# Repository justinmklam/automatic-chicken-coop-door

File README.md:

# Automatic Chicken Coop Door

Automatic chicken coop door for my backyard egg layers. Modeled after the commercially available [Chicken Guard](https://www.chickenguard.com/).

## Parts List
- Arduino Pro Mini
- Monochrome 128x32 I2C OLED
- DS3231 RTC with CR2032 Battery
- 6V 10rpm 25GA Brushed DC Motor
- TB6612FNG Motor Driver
- XL6009 Buck Boost Module

## Dependencies
- [Low Power](https://github.com/rocketscream/Low-Power)
- [Motor Driver TB6612FNG](https://github.com/sparkfun/SparkFun_TB6612FNG_Arduino_Library)
- [FabioCuomo-DS3231](https://github.com/FabioCuomo/FabioCuomo-DS3231)
- [SSD1306 1.2.9](https://github.com/adafruit/Adafruit_SSD1306)
- [GFX 1.4.2](https://github.com/adafruit/Adafruit-GFX-Library)

## How It Works

The main program sets alarms to wake up from sleep based on sunrise/sunset times (from [here](https://www.timeanddate.com/sun/canada/vancouver?month=1&year=2019)). These times are consistent year after year, and is more reliable than using a light sensor which can be finicky to adjust for street lamps, headlights from passing cars, etc.

## Power Consumption

- Powered on = 18.35 mA
- Motor on = 320 mA (no load), ~700 mA (load)
- Sleep = 0.94 mA

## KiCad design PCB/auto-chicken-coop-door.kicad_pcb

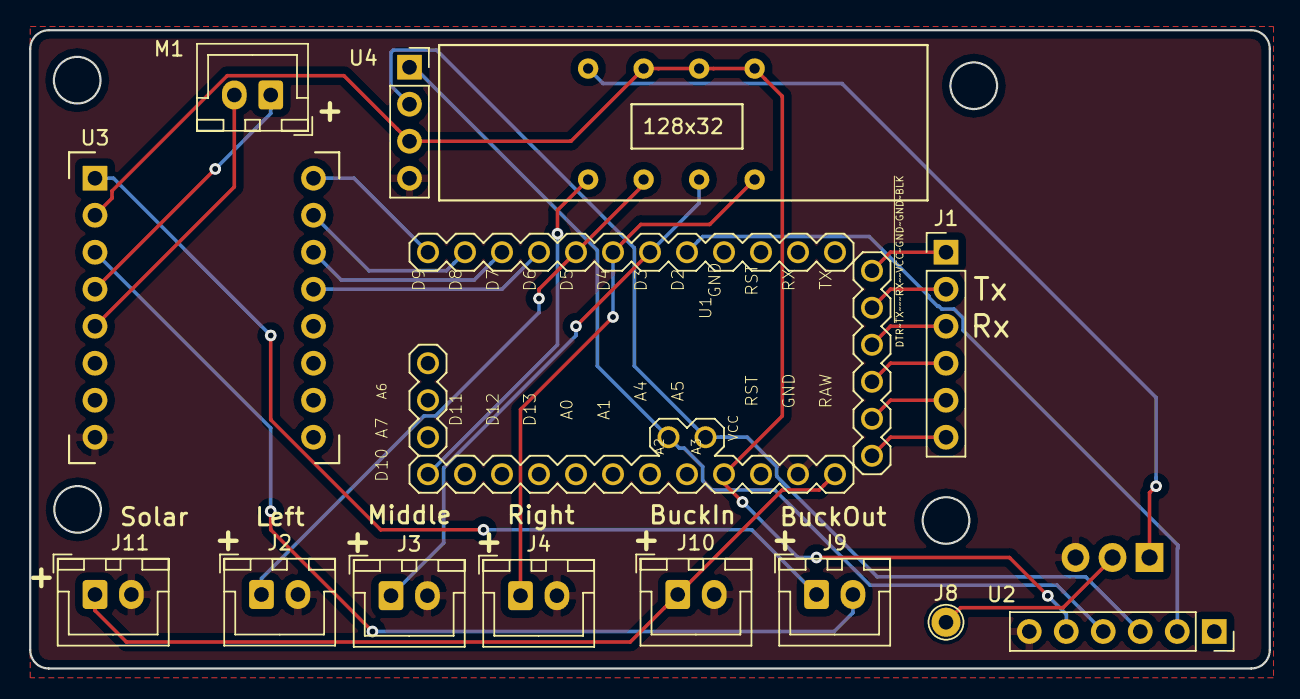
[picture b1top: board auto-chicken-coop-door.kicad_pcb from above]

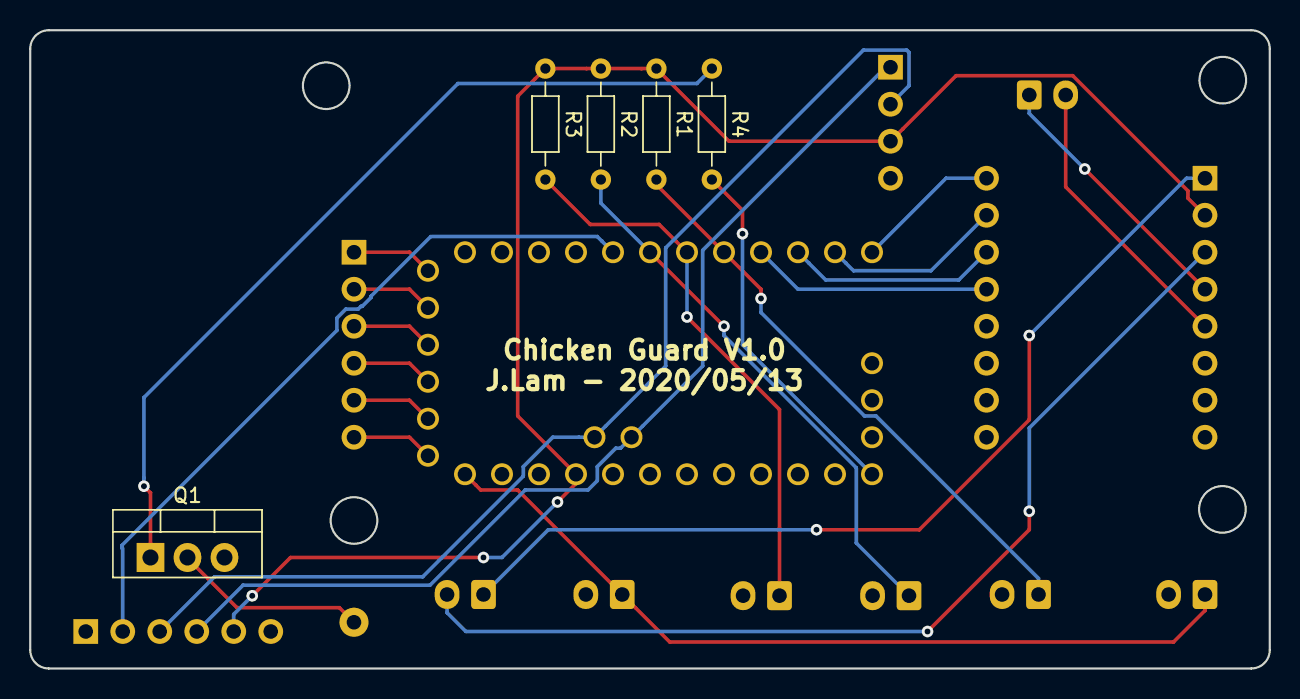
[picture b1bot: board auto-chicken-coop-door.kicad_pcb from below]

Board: 2 copper layers, 85.1 x 43.8 mm, 18 parts (5 on the bottom side), 26 nets.

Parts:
J1: Programming_Headers; PinHeader_1x06_P2.54mm_Vertical
J2: Conn_Left; JST_XH_B02B-XH-A_1x02_P2.50mm_Vertical
J3: Conn_Middle; JST_XH_B02B-XH-A_1x02_P2.50mm_Vertical
J4: Conn_Right; JST_XH_B02B-XH-A_1x02_P2.50mm_Vertical
J8: Conn_01x01; TestPoint_THTPad_D2.0mm_Drill1.0mm
J9: BuckBoost; JST_XH_B02B-XH-A_1x02_P2.50mm_Vertical
J10, J11: Charger; JST_XH_B02B-XH-A_1x02_P2.50mm_Vertical
M1: Motor_DC; JST_XH_B02B-XH-A_1x02_P2.50mm_Vertical
Q1: TIP122; TO-220-3_Vertical
R1, R2, R3: 10k; R_Axial_DIN0204_L3.6mm_D1.6mm_P7.62mm_Horizontal
R4: 1k; R_Axial_DIN0204_L3.6mm_D1.6mm_P7.62mm_Horizontal
U1: Arduino_Pro_Mini; ArduinoProMini
U2: DS3231; PinSocket_1x06_P2.54mm_Vertical
U3: Sparkfun_Dual_Motor_Driver_TB6612FNG; Sparkfun_TB6612FNG
U4: SSD1306_OLED_128x32; SSD1306_Adafruit_128x32

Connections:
D3: J3.1, R2.2, U1.D3
D4: J4.1, R3.2, U1.D4
D5: J2.1, R1.2, U1.D5
D10: R4.2, U1.D10
GND: J2.2, J3.2, J4.2, J10.2, J11.2, Q1.3, U1.GND@1, U2.6, U3.8, U4.4
unnamed: J1.1, U1.DTR
unnamed: J1.2, U1.TX@1
unnamed: J1.3, U1.RX@1
unnamed: J1.4, U1.VCC@1
unnamed: J1.5, U1.GND@2
unnamed: J1.6, U1.BLK
unnamed: J8.1, Q1.2
unnamed: J9.1, U3.1
unnamed: J9.2, U3.3
unnamed: J10.1, J11.1, U1.RAW
unnamed: M1.1, U3.4
unnamed: M1.2, U3.5
unnamed: Q1.1, R4.1
unnamed: U1.D2, U2.2
unnamed: U1.D6, U3.12
unnamed: U1.D7, U3.11
unnamed: U1.D8, U3.10
unnamed: U1.D9, U3.9
SCL: U1.A5, U2.3, U4.2
SDA: U1.A4, U2.4, U4.1
VCC: R1.1, R2.1, R3.1, U1.VCC, U2.5, U3.2, U4.3

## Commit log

2019-03-03 Add test code for controlling motor driver
2019-03-04 Add motor firmware settings from config utility
2019-03-09 Refactor motor control methods and base sketch
2019-03-09 Refactor motor control to class
2019-03-09 Final working demo implemented
2019-03-09 Move defines to header; rename move() to setSpeed()
2019-03-09 Add vscode project settings
2019-03-09 Trim trailing whitespace
2019-03-15 Add 3D print models for motor spool
2019-03-15 Initial commit of main controller sketch
2019-03-20 Add arduino libraries to path
2019-03-20 Use RTClibExtended for alarms; add low power example
2019-03-20 Change date/timestamp methods to directly return the string
2019-03-22 Move clear_alarms() to begin()
2019-03-22 Add wrapper class for ssd1306 display
2019-03-22 Minor fixes to display and rtc functions
2019-03-22 Reordered include paths so manually downloaded libs are found first
2019-03-22 Add wrapper class for motor control
    Should refactor class to use inheritance instead
2019-03-23 Pad date/time formats with leading 0
2019-03-23 Add basic button functionality
2019-03-23 Change defined variables to const
2019-03-23 Add proper display sleep method
    Reduces sleep consumption from ~2mA to ~0.8mA
2019-03-23 Fix millis() interval check to handle rollover
2019-03-23 Minor improvements to rtc and display methods
    Replace malloc with input buffer so don't need to free memory. Was
    causing timestamp to not show on display after a few mins.
    Remove display() from methods to prevent double refresh.
    Moved global variables to loop(), but didn't seem to affect memory.
2019-03-23 Move standby calls to functions; add initial inactive sleep method
2019-03-24 [major] Refactor using task schedulers
2019-03-24 Add build output
2019-03-24 Minor reformatting changes
2019-03-24 Separate sleep mode from inactivity and alarm
    Also add inactivity sleep to user input
2019-03-25 Add preliminary door calibration method
2019-04-09 Add ipch files to gitignore
2019-04-09 Implement basic door open/close and calibration method
2019-04-09 Save calibrated distance to eeprom
2019-04-09 Activate calibration after 2 second button press
2019-04-09 Move door calibration to separate function
2019-04-09 Move custom eeprom methods to separate file
2019-04-09 Rename constants to upper case
2019-04-09 [major] Create door control triggered task
2019-04-09 Add RTC getter for now()
2019-04-09 Initial commit of sunrise/sunset alarm class (untested)
2019-04-09 Fix logic for sunrise/sunset alarms
2019-04-09 [major] Add logger
2019-04-09 Add door control after waking from sleep
2019-04-09 Add note to logger
2019-04-09 Show next alarm on main display
2019-04-09 Write door open/close status to EEPROM
2019-04-10 Fix garbage display output
2019-04-10 Add TODO about artifacts on screen
2019-04-10 Minor edits to logger
2019-04-10 Minor formatting edits
2019-04-10 [bugfix] Correct current time check so next alarm is set correctly
2019-04-10 Autoformat documents
2019-04-10 Rename driver files
2019-04-10 Move jrk21v3 config to sketch folder
2019-04-10 Rename project folder
2019-04-10 Reduce frequency of alarm set
2019-04-10 Move jrk21v3 demo to separate repository
2019-04-10 Added image of chickens to README
2019-04-10 Add TODO for daylight savings
2019-04-10 Change sunset buffer hour from 2 to 1
    Since it's pretty dark 2 hours after sunset, and the hens are sleeping already
2019-04-10 [bugfix] Add logic check for before sunrise/after sunset
    Previously would fail if since both minute and hour had to be greater
    (which is incorrect)
2019-04-11 [bugfix] Subtle fix so before sunrise check is correct
2019-04-11 [major] Add daylight saving button toggle
    Also had to disable the logger since it was causing the scheduler to
    fail halfway (for some unknown reason)
2019-04-12 Add door state to EEPROM
2019-04-14 Don't write door calibration if unchanged
2019-04-14 Fix motor direction to consistent behaviour
2019-04-14 Add delay after each calibration state change
    Also don't trigger inactivity monitor during calibration mode
2019-04-14 Reverse motor direction so it's correct with open/close of door
2019-04-28 Initial commit for KiCad schematic files
2019-04-28 Change buttons to connectors
2019-04-28 Add pushbuttons; add motor input voltage to 7.5V
2019-04-28 Update title block info
2019-04-28 Add schematic pdf
2019-05-29 Update motor spool model for 3D printing
2019-05-29 Add TIP122 and buck/boost module to schematic
2019-05-29 Add motor power transistor
2019-05-29 Update dependencies in README
2019-05-29 Update schematic
2019-05-29 Resave kicad files from crash
2019-05-29 [bugfix] Middle button must be on pin 3 for interrupt
2019-05-29 Remove logger statements causing issues
    Reduce the number of serial prints at the beginning, otherwise it crashes
2019-05-29 Update pin definitions
2019-06-04 Disable motor in constructor; reverse logic
    Use NPN transistor to enable/disable the XL6009 buck/boost converter
2019-06-04 Add parts and power consumption to README
2019-06-04 Update schematic with pins and correct transistor config
    Use TIP122 to enable/disable the XL6009 module. Doesn't work if enable is connected
    directly to pin 10.
2020-05-14 Add footprints to schematic
2020-05-14 PCB layout complete
2020-05-14 Add silkscreen labels
2020-05-14 Add gerbers
2020-05-14 Add ground plane
2020-05-14 Export gerbers
2020-05-14 Add zip files to gitignore
2020-05-14 Fix overlapping traces with pad
